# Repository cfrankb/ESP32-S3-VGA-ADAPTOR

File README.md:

# Architectural Shift

Implementing a discrete DAC R-2R allows for full control over the signal chain and demonstrates the ability to interface digital MCUs with legacy analog standards without relying on specialized external ICs

# Encoding

Colors are encoded as unsigned 16bits integer (B5G6R5).

The five (5) lowest bits are red and in accending order of brigtness. The next six (6) bits are green and the last five (5) bits are blue.

# Schematic

# Hardware

## ESP32-S3

Recommended ESP32S3 DevKit.

https://vi.aliexpress.com/item/1005006418608267.html

## Dupont cables

https://www.aliexpress.com/item/1005004611997111.html

## VGA Adaptor

An adaptor is needed to communicate with the VGA Hardware.

### Manually assembled

Create a resistor ladder wire. Connect all the pins of the same color together.

| GPIO Pin | Role  | Resistor | VGA Pin |
| -------- | ----- | -------- | ------- |
| 1        | hsync | 47R      | 13      |
| 2        | vsync | 47R      | 14      |
| 4        | red   | 8k       | 1       |
| 5        | red   | 4k       |
| 6        | red   | 2k       |
| 7        | red   | 1k       |
| 8        | red   | 512R     |
| 9        | green | 16k  *   | 2       |
| 10       | green | 8k       |
| 11       | green | 4k       |
| 12       | green | 2k       |
| 13       | green | 1k       |
| 14       | green | 512R     |
| 15       | blue  | 8k       | 3       |
| 16       | blue  | 4k       |
| 17       | blue  | 2k       |
| 18       | blue  | 1k       |
| 21       | blue  | 512R     |
| GND      | -     | -        | 5, 10   |

\* If you don't have any 16k Resistor. You can use a similar value such as 20k. The smallest resistor is the most significant and should be roughtly ~500R or higher.

VGA Connector: [DB15 to Dip 2.54mm interface ](https://vi.aliexpress.com/item/1005005279582020.html)

## Demo Project

Gameplay: https://www.youtube.com/watch?v=SPQwWkzFRpU

Source code: [cfrankb/ESP32-S3-VGA-CS3](https://github.com/cfrankb/ESP32-S3-VGA-CS3)

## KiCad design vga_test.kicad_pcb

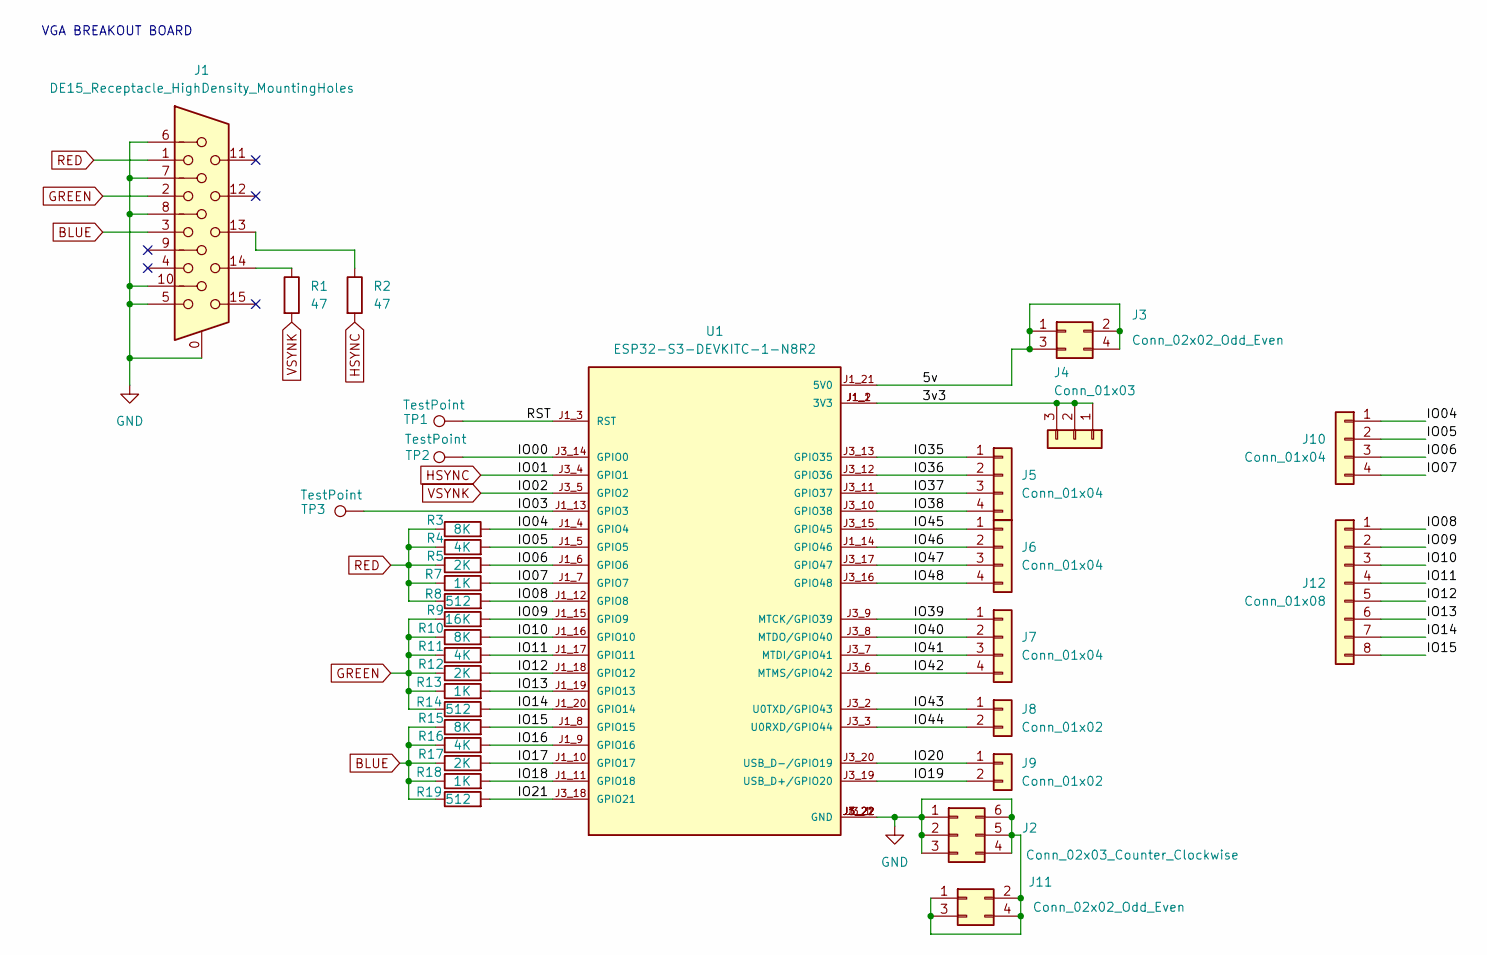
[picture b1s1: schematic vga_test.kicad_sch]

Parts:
J1: DE15_Receptacle_HighDensity_MountingHoles; DSUB-15-L77HDE15SD1CH4F
J2: Conn_02x03_Counter_Clockwise; PinHeader_2x03_P2.54mm_Vertical
J3, J11: Conn_02x02_Odd_Even; PinHeader_2x02_P2.54mm_Vertical
J4: Conn_01x03; PinHeader_1x03_P2.54mm_Vertical
J5, J6, J7, J10: Conn_01x04; PinHeader_1x04_P2.54mm_Vertical
J8, J9: Conn_01x02; PinHeader_1x02_P2.54mm_Vertical
J12: Conn_01x08; PinHeader_1x08_P2.54mm_Vertical
R1, R2: 47; R_0805_2012Metric_Pad1.20x1.40mm_HandSolder
R3, R10, R15: 8K; R_0805_2012Metric_Pad1.20x1.40mm_HandSolder
R4, R11, R16: 4K; R_0805_2012Metric_Pad1.20x1.40mm_HandSolder
R5, R12, R17: 2K; R_0805_2012Metric_Pad1.20x1.40mm_HandSolder
R7, R13, R18: 1K; R_0805_2012Metric_Pad1.20x1.40mm_HandSolder
R8, R14, R19: 512; R_0805_2012Metric_Pad1.20x1.40mm_HandSolder
R9: 16K; R_0805_2012Metric_Pad1.20x1.40mm_HandSolder
TP1, TP2, TP3: TestPoint; TestPoint_Pad_1.0x1.0mm
U1: ESP32-S3-DEVKITC-1-N8R2; ESP32-S3-WROOM1; PARTREV V1

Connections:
/3v3: J4.1, J4.2, J4.3, U1.J1_1 (3V3), U1.J1_2 (3V3)
/5v: J3.1, J3.2, J3.3, J3.4, U1.J1_21 (5V0)
/IO00: TP2.1, U1.J3_14 (GPIO0)
/IO03: TP3.1, U1.J1_13 (GPIO3)
/IO04: J10.1, R3.2, U1.J1_4 (GPIO4)
/IO05: J10.2, R4.2, U1.J1_5 (GPIO5)
/IO06: J10.3, R5.2, U1.J1_6 (GPIO6)
/IO07: J10.4, R7.2, U1.J1_7 (GPIO7)
/IO08: J12.1, R8.2, U1.J1_12 (GPIO8)
/IO09: J12.2, R9.2, U1.J1_15 (GPIO9)
/IO10: J12.3, R10.2, U1.J1_16 (GPIO10)
/IO11: J12.4, R11.2, U1.J1_17 (GPIO11)
/IO12: J12.5, R12.2, U1.J1_18 (GPIO12)
/IO13: J12.6, R13.2, U1.J1_19 (GPIO13)
/IO14: J12.7, R14.2, U1.J1_20 (GPIO14)
/IO15: J12.8, R15.2, U1.J1_8 (GPIO15)
/IO16: R16.2, U1.J1_9 (GPIO16)
/IO17: R17.2, U1.J1_10 (GPIO17)
/IO18: R18.2, U1.J1_11 (GPIO18)
/IO19: J9.2, U1.J3_19 (USB_D+/GPIO20)
/IO20: J9.1, U1.J3_20 (USB_D-/GPIO19)
/IO21: R19.2, U1.J3_18 (GPIO21)
/IO35: J5.1, U1.J3_13 (GPIO35)
/IO36: J5.2, U1.J3_12 (GPIO36)
/IO37: J5.3, U1.J3_11 (GPIO37)
/IO38: J5.4, U1.J3_10 (GPIO38)
/IO39: J7.1, U1.J3_9 (MTCK/GPIO39)
/IO40: J7.2, U1.J3_8 (MTDO/GPIO40)
/IO41: J7.3, U1.J3_7 (MTDI/GPIO41)
/IO42: J7.4, U1.J3_6 (MTMS/GPIO42)
/IO43: J8.1, U1.J3_2 (U0TXD/GPIO43)
/IO44: J8.2, U1.J3_3 (U0RXD/GPIO44)
/IO45: J6.1, U1.J3_15 (GPIO45)
/IO46: J6.2, U1.J1_14 (GPIO46)
/IO47: J6.3, U1.J3_17 (GPIO47)
/IO48: J6.4, U1.J3_16 (GPIO48)
/RST: TP1.1, U1.J1_3 (RST)
BLUE: J1.3, R15.1, R16.1, R17.1, R18.1, R19.1
GND: J1.0, J1.5, J1.6, J1.7, J1.8, J1.10, J2.1, J2.2, J2.3, J2.4, J2.5, J2.6, J11.1, J11.2, J11.3, J11.4, U1.J1_22 (GND), U1.J3_1 (GND), U1.J3_21 (GND), U1.J3_22 (GND)
GREEN: J1.2, R9.1, R10.1, R11.1, R12.1, R13.1, R14.1
HSYNC: R2.2, U1.J3_4 (GPIO1)
unnamed: J1.13, R2.1
unnamed: J1.14, R1.1
RED: J1.1, R3.1, R4.1, R5.1, R7.1, R8.1
VSYNK: R1.2, U1.J3_5 (GPIO2)

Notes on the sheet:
VGA BREAKOUT BOARD

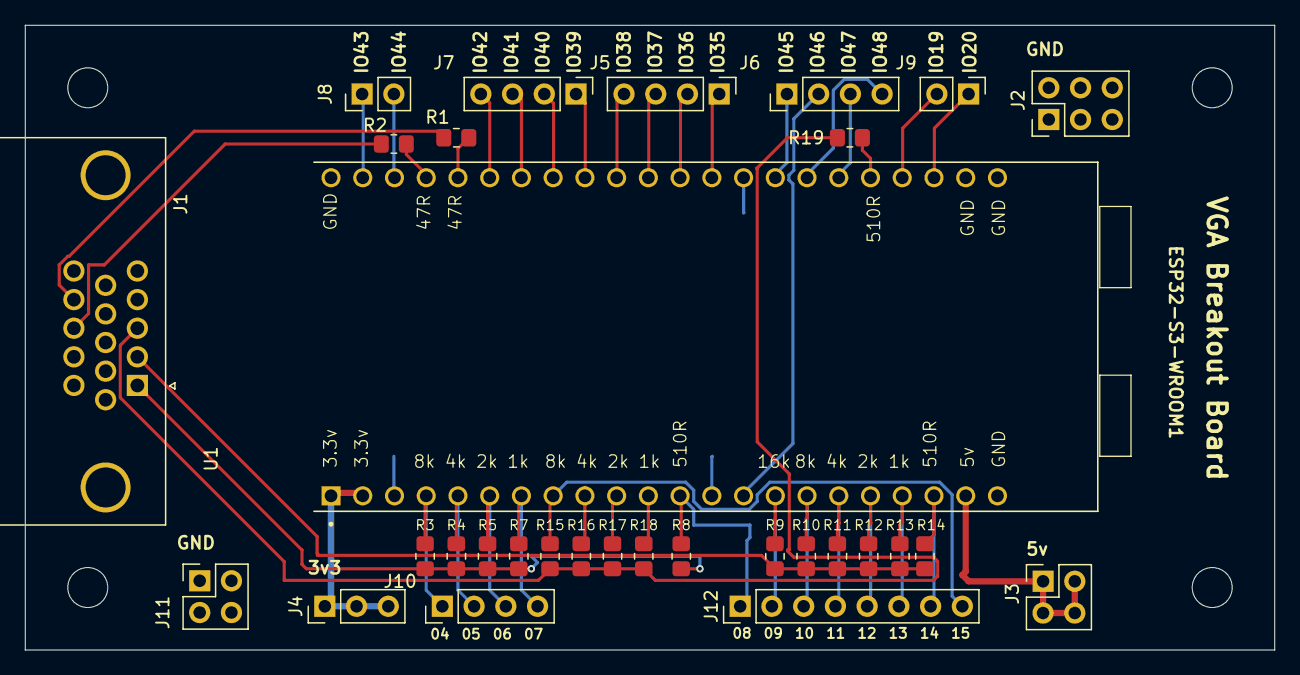
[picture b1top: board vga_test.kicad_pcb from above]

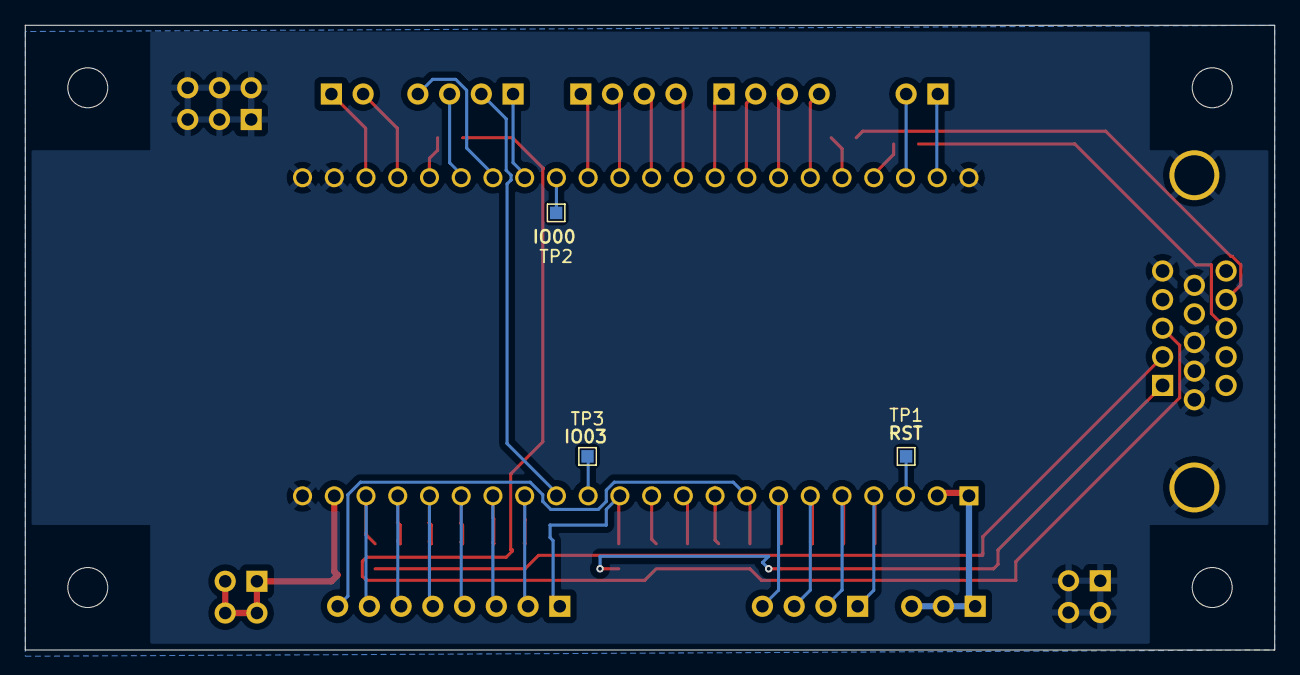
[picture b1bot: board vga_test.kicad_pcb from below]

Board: 2 copper layers, 100.0 x 50.0 mm, 38 parts (3 on the bottom side), 45 nets.

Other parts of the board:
H3, H3#2, H3#3, H3#4: MountingHole; MountingHole_3.2mm_M3

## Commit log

2025-01-23 added README
2025-02-03 added picture and gerber
2025-02-03 added dsub15 footprint
2026-03-05 added schematic
2026-03-05 small change
2026-03-05 added more text
